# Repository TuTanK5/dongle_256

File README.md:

# dongle_256
Split BLE low profile keyboard using Nordic nRF52840 dongle PCA10059

(WIP) Firmware guide

Flash new bootloader:

We need UF2 bootloader to support CircuitPython. The PCA10059 isn't shipped with UF2, hence we have to flash it.

Lastest UF2 bootloader should be listed at: https://github.com/adafruit/Adafruit_nRF52_Bootloader/releases (go to assets and find pca10059, download the hex file)

If you have a Raspberry Pi you can follow this guide to flash it. (Tested with Raspberry Pi 4)

https://www.rototron.info/circuitpython-nrf52840-dongle-openocd-pi-tutorial/

OR if you have an STLink-V2 debugger:

Install STLink driver:

https://www.st.com/en/development-tools/stsw-link009.html#get-software

Get and use OpenOCD with STLink:

https://github.com/seemoo-lab/openhaystack/wiki/Flashing-nRF-with-OpenOCD---ST-Link

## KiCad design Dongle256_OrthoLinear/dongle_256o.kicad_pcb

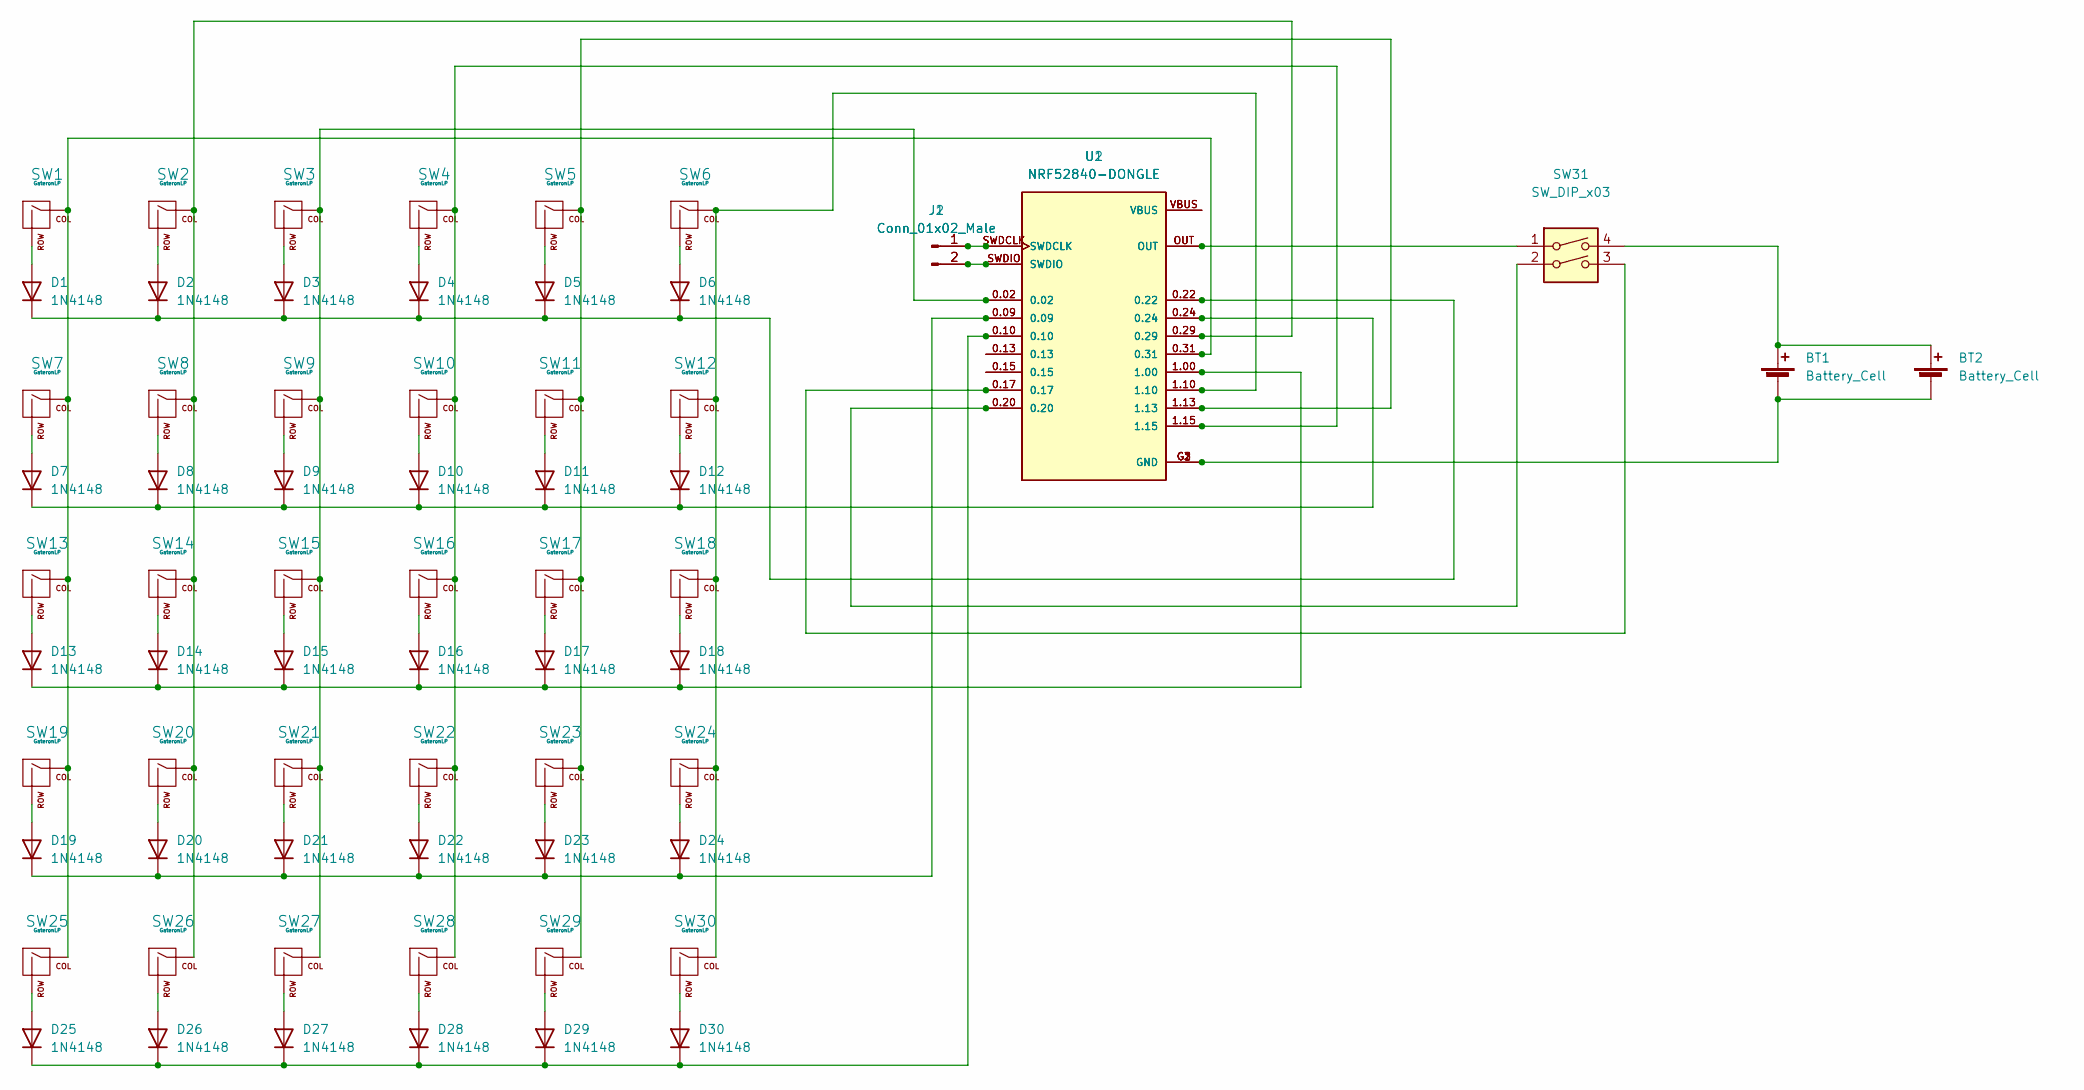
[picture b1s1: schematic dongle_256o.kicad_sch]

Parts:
BT1, BT2: Battery_Cell; TBH-CR2032-M04
D1, D2, D3, D4, D5, D6, D7, D8, D9, D10, D11, D12, D13, D14, D15, D16, D17, D18, D19, D20, D21, D22, D23, D24, D25, D26, D27, D28, D29, D30: 1N4148; D_DO-35_SOD27_P7.62mm_Horizontal
J1, J2: Conn_01x02_Male; PinHeader_1x02_P2.54mm_Vertical
SW1, SW2, SW3, SW4, SW5, SW6, SW7, SW8, SW9, SW10, SW11, SW12, SW13, SW14, SW15, SW16, SW17, SW18, SW19, SW20, SW21, SW22, SW23, SW24, SW25, SW26, SW27, SW28, SW29, SW30: GateronLP; Gateron_low_profile_reversible
SW31: SW_DIP_x03; SW_DIP_SPSTx03_Slide_9.78x9.8mm_W7.62mm_P2.54mm
U1, U2: NRF52840-DONGLE; MODULE_NRF52840-DONGLE; PARTREV 1.1

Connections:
unnamed: BT1.1 (+), BT2.1 (+), SW31.4
unnamed: BT1.2 (-), BT2.2 (-), U1.G1 (GND), U1.G2 (GND), U1.G3 (GND), U2.G1 (GND), U2.G2 (GND), U2.G3 (GND)
unnamed: D1.1 (K), D2.1 (K), D3.1 (K), D4.1 (K), D5.1 (K), D6.1 (K), U1.0.22, U2.0.22
unnamed: D1.2 (A), SW1.2 (ROW)
unnamed: D2.2 (A), SW2.2 (ROW)
unnamed: D3.2 (A), SW3.2 (ROW)
unnamed: D4.2 (A), SW4.2 (ROW)
unnamed: D5.2 (A), SW5.2 (ROW)
unnamed: D6.2 (A), SW6.2 (ROW)
unnamed: D7.2 (A), SW7.2 (ROW)
unnamed: D8.2 (A), SW8.2 (ROW)
unnamed: D9.2 (A), SW9.2 (ROW)
unnamed: D7.1 (K), D8.1 (K), D9.1 (K), D10.1 (K), D11.1 (K), D12.1 (K), U1.0.24, U2.0.24
unnamed: D10.2 (A), SW10.2 (ROW)
unnamed: D11.2 (A), SW11.2 (ROW)
unnamed: D12.2 (A), SW12.2 (ROW)
unnamed: D13.1 (K), D14.1 (K), D15.1 (K), D16.1 (K), D17.1 (K), D18.1 (K), U1.1.00, U2.1.00
unnamed: D13.2 (A), SW13.2 (ROW)
unnamed: D14.2 (A), SW14.2 (ROW)
unnamed: D15.2 (A), SW15.2 (ROW)
unnamed: D16.2 (A), SW16.2 (ROW)
unnamed: D17.2 (A), SW17.2 (ROW)
unnamed: D18.2 (A), SW18.2 (ROW)
unnamed: D19.1 (K), D20.1 (K), D21.1 (K), D22.1 (K), D23.1 (K), D24.1 (K), U1.0.09, U2.0.09
unnamed: D19.2 (A), SW19.2 (ROW)
unnamed: D20.2 (A), SW20.2 (ROW)
unnamed: D21.2 (A), SW21.2 (ROW)
unnamed: D22.2 (A), SW22.2 (ROW)
unnamed: D23.2 (A), SW23.2 (ROW)
unnamed: D24.2 (A), SW24.2 (ROW)
unnamed: D25.1 (K), D26.1 (K), D27.1 (K), D28.1 (K), D29.1 (K), D30.1 (K), U1.0.10, U2.0.10
unnamed: D25.2 (A), SW25.2 (ROW)
unnamed: D26.2 (A), SW26.2 (ROW)
unnamed: D27.2 (A), SW27.2 (ROW)
unnamed: D28.2 (A), SW28.2 (ROW)
unnamed: D29.2 (A), SW29.2 (ROW)
unnamed: D30.2 (A), SW30.2 (ROW)
unnamed: J1.1, J2.1, U1.SWDCLK, U2.SWDCLK
unnamed: J1.2, J2.2, U1.SWDIO, U2.SWDIO
unnamed: SW1.1 (COL), SW7.1 (COL), SW13.1 (COL), SW19.1 (COL), SW25.1 (COL), U1.0.31, U2.0.31
unnamed: SW4.1 (COL), SW10.1 (COL), SW16.1 (COL), SW22.1 (COL), SW28.1 (COL), U1.1.15, U2.1.15
unnamed: SW5.1 (COL), SW11.1 (COL), SW17.1 (COL), SW23.1 (COL), SW29.1 (COL), U1.1.13, U2.1.13
unnamed: SW6.1 (COL), SW12.1 (COL), SW18.1 (COL), SW24.1 (COL), SW30.1 (COL), U1.1.10, U2.1.10
unnamed: SW2.1 (COL), SW8.1 (COL), SW14.1 (COL), SW20.1 (COL), SW26.1 (COL), U1.0.29, U2.0.29
unnamed: SW3.1 (COL), SW9.1 (COL), SW15.1 (COL), SW21.1 (COL), SW27.1 (COL), U1.0.02, U2.0.02
unnamed: SW31.1, U1.OUT, U2.OUT
unnamed: SW31.2, U1.0.20, U2.0.20
unnamed: SW31.3, U1.0.17, U2.0.17
unnamed: U1.0.13, U2.0.13
unnamed: U1.0.15, U2.0.15
unnamed: U1.VBUS, U2.VBUS

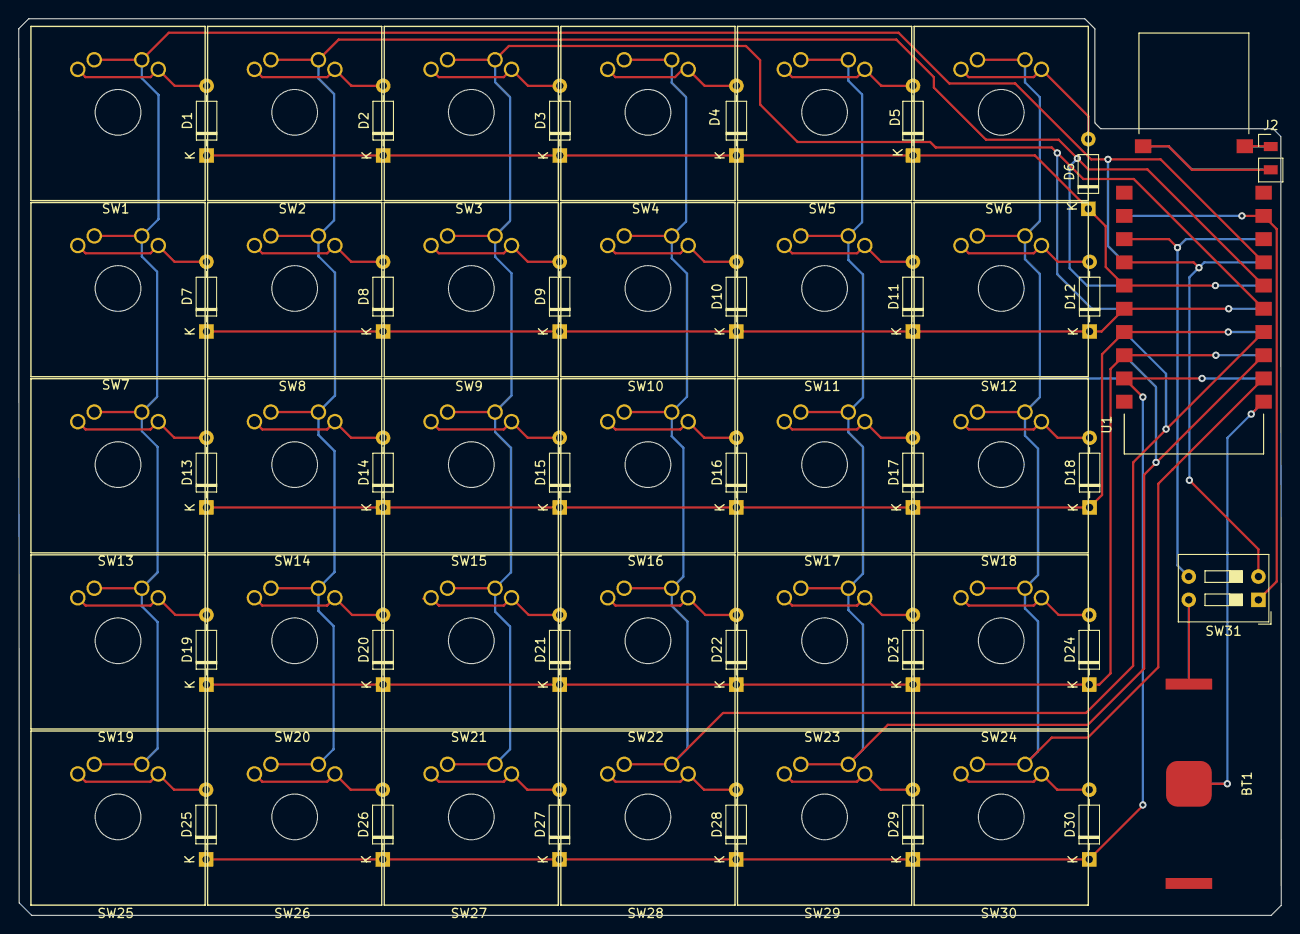
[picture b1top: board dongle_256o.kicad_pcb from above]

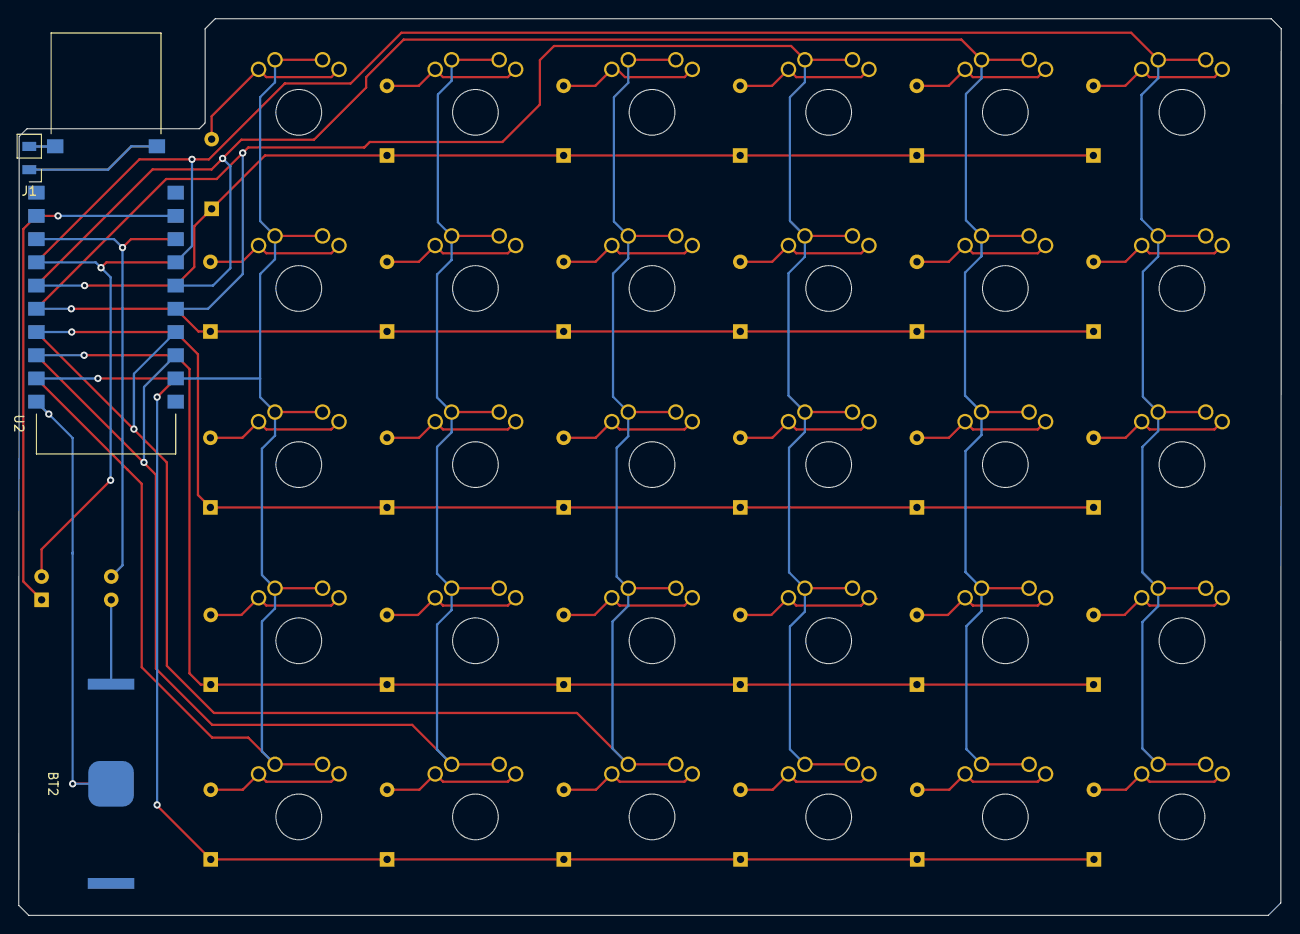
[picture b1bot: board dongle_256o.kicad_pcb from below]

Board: 2 copper layers, 138.1 x 98.1 mm, 67 parts (3 on the bottom side), 51 nets.

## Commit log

2022-11-05 initial kicad pro
2022-11-28 temporary commit 20221128
2022-12-13 PCB design without switch
2022-12-19 Update on off and slider switch
2022-12-25 remove backups from git
2023-01-02 Update flashing pads and redo the status switch.
2023-01-04 Move battery holder of columnStaggered PCB up away from thumb key
2023-02-14 Finalize design and generate gerber
2023-02-15 Touch up, reorder and zip gbr files
